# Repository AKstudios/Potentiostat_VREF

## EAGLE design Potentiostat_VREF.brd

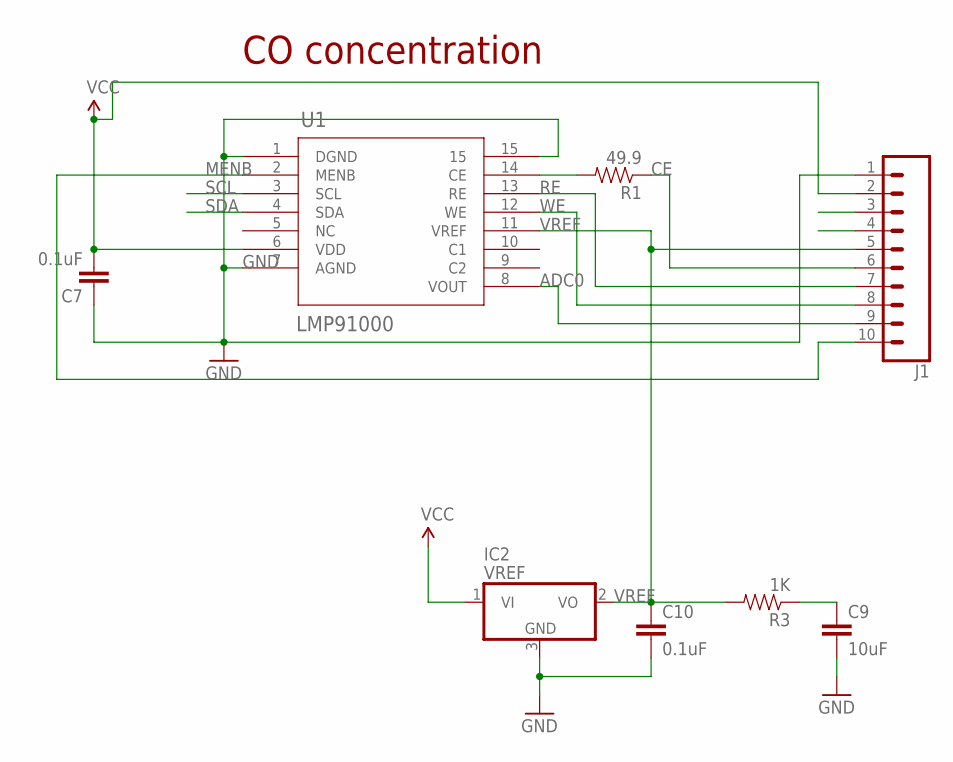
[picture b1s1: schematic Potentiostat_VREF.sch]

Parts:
C7, C10: 0.1uF; 0805; MPN AC0805KRX7R9BB104
C9: 10uF; 0805; MPN CC0805ZKY5V6BB106
IC2: VREF; SOT23; MPN ISL60002DIH320Z-TK
J1: CONN_10"; 1X10
R1: 49.9; 0805; MPN RC0805FR-0749R9L
R3: 1K; 0805; MPN RC0805JR-071KL
U1: LMP91000; SDA14B; MPN LMP91000

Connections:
ADC0: J1.9, U1.8 (VOUT)
CE: J1.6, R1.1
GND: C7.1, C9.2, C10.2, IC2.3 (GND), J1.1, U1.1 (DGND), U1.7 (AGND), U1.15
MENB: J1.10, U1.2 (MENB)
unnamed: R1.2, U1.14 (CE)
unnamed: C9.1, R3.1
RE: J1.7, U1.13 (RE)
SCL: U1.3 (SCL)
SDA: U1.4 (SDA)
VCC: C7.2, IC2.1 (VI), J1.2, U1.6 (VDD)
VREF: C10.1, IC2.2 (VO), J1.5, R3.2, U1.11 (VREF)
WE: J1.8, U1.12 (WE)

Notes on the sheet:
CO concentration

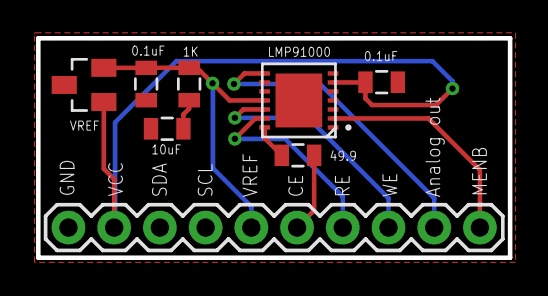
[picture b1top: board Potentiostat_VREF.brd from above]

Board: 2 copper layers, 26.2 x 12.2 mm, 8 parts (0 on the bottom side), 10 nets.

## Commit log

2017-07-20 :neckbeard: Added .gitattributes & .gitignore files
2017-07-20 init

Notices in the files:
parts and their libraries:
SparkFun-Passives: Licensing: Creative Commons ShareAlike 4.0 International - https://creativecommons.org/licenses/by-sa/4.0
